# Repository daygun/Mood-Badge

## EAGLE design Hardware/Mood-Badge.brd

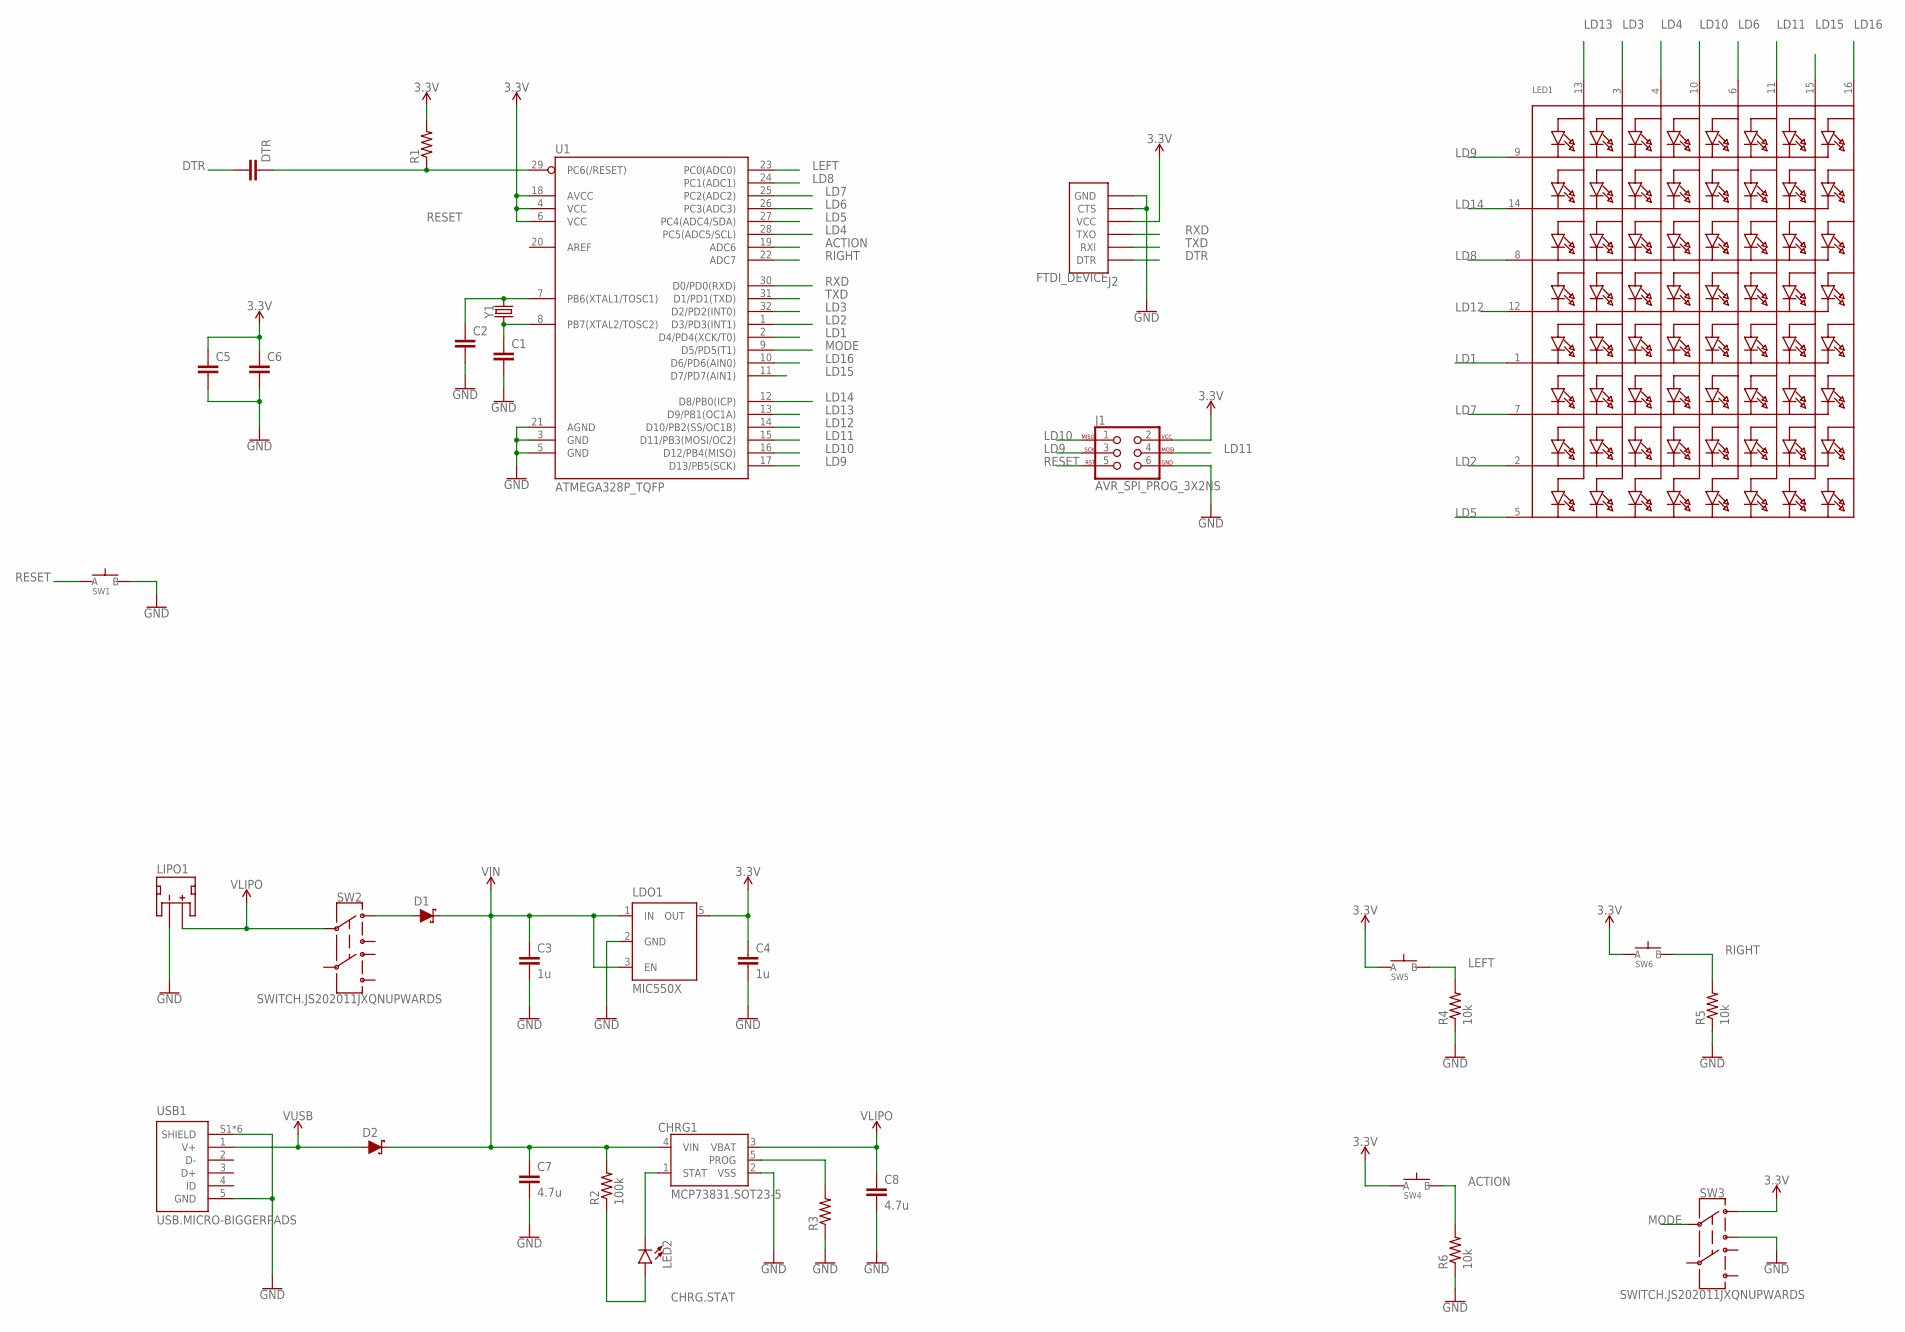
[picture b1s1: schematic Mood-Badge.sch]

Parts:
C1, C2, C5, C6: CAPACITOR0603; C0603
C3, C4: 1u; C0603
C7, C8: 4.7u; C0603
CHRG1: MCP73831.SOT23-5; SOT23-5
D1, D2: SCHOTTKY-USC; USC
DTR: CAPACITOR0603; C0603
J1: AVR_SPI_PROG_3X2NS; 2X3-NS
J2: FTDI_DEVICE
LDO1: MIC550X; SOT23-5
LED1: DOTMATRIX_8X8_ROWCATHODEM12A881UR; DOTMATRIX_BL-M12A881UR
LED2: LED0805; LED-0805
LIPO1: JST_2MM_MALE; JST-2-SMD
R1, R3: RESISTOR0603; R0603
R2: 100k; R0603
R4, R5, R6: 10k; R0603
SW1, SW4, SW5, SW6: SPST.KT11P4SM34LFS
SW2, SW3: SWITCH.JS202011JXQNUPWARDS; SWITCH.00
U1: ATMEGA328P_TQFP; TQFP32-08
USB1: USB.MICRO-BIGGERPADS; USB-MICRO-01.BIGGERPADS
Y1: CRYSTAL-CA-310; CA-301

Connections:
3.3V: C4.1, C5.1, C6.1, J1.2, J2.VCC, LDO1.5 (OUT), R1.2, SW3.1, SW4.1 (A), SW4.2 (A), SW5.1 (A), SW5.2 (A), SW6.1 (A), SW6.2 (A), U1.4 (VCC), U1.6 (VCC), U1.18 (AVCC)
ACTION: R6.2, SW4.3 (B), SW4.4 (B), U1.19 (ADC6)
CHRG.STAT: LED2.A, R2.1
DTR: DTR.1, J2.DTR
GND: C1.2, C2.2, C3.2, C4.2, C5.2, C6.2, C7.2, C8.2, CHRG1.2 (VSS), J1.6, J2.CTS, J2.GND, LDO1.2 (GND), LIPO1.1 (-), R3.1, R4.1, R5.1, R6.1, SW1.3 (B), SW1.4 (B), SW3.3, U1.3 (GND), U1.5 (GND), U1.21 (AGND), USB1.5 (GND), USB1.S1 (SHIELD), USB1.S2 (SHIELD), USB1.S3 (SHIELD), USB1.S4 (SHIELD), USB1.S5 (SHIELD), USB1.S6 (SHIELD)
LD1: LED1.1 (K5), U1.2 (D4/PD4(XCK/T0))
LD2: LED1.2 (K7), U1.1 (D3/PD3(INT1))
LD3: LED1.3 (A2), U1.32 (D2/PD2(INT0))
LD4: LED1.4 (A3), U1.28 (PC5(ADC5/SCL))
LD5: LED1.5 (K8), U1.27 (PC4(ADC4/SDA))
LD6: LED1.6 (A5), U1.26 (PC3(ADC3))
LD7: LED1.7 (K6), U1.25 (PC2(ADC2))
LD8: LED1.8 (K3), U1.24 (PC1(ADC1))
LD9: J1.3, LED1.9 (K1), U1.17 (D13/PB5(SCK))
LD10: J1.1, LED1.10 (A4), U1.16 (D12/PB4(MISO))
LD11: J1.4, LED1.11 (A6), U1.15 (D11/PB3(MOSI/OC2))
LD12: LED1.12 (K4), U1.14 (D10/PB2(SS/OC1B))
LD13: LED1.13 (A1), U1.13 (D9/PB1(OC1A))
LD14: LED1.14 (K2), U1.12 (D8/PB0(ICP))
LD15: LED1.15 (A7), U1.11 (D7/PD7(AIN1))
LD16: LED1.16 (A8), U1.10 (D6/PD6(AIN0))
LEFT: R4.2, SW5.3 (B), SW5.4 (B), U1.23 (PC0(ADC0))
MODE: SW3.2, U1.9 (D5/PD5(T1))
unnamed: C1.1, U1.8 (PB7(XTAL2/TOSC2)), Y1.1
unnamed: CHRG1.1 (STAT), LED2.C
unnamed: D1.+ (A), SW2.1
unnamed: C2.1, U1.7 (PB6(XTAL1/TOSC1)), Y1.2
unnamed: CHRG1.5 (PROG), R3.2
RESET: DTR.2, J1.5, R1.1, SW1.1 (A), SW1.2 (A), U1.29 (PC6(/RESET))
RIGHT: R5.2, SW6.3 (B), SW6.4 (B), U1.22 (ADC7)
RXD: J2.RXI (TXO), U1.30 (D0/PD0(RXD))
TXD: J2.TXO (RXI), U1.31 (D1/PD1(TXD))
VIN: C3.1, C7.1, CHRG1.4 (VIN), D1.- (C), D2.- (C), LDO1.1 (IN), LDO1.3 (EN), R2.2
VLIPO: C8.1, CHRG1.3 (VBAT), LIPO1.2 (+), SW2.2
V_USB: D2.+ (A), USB1.1 (V+)

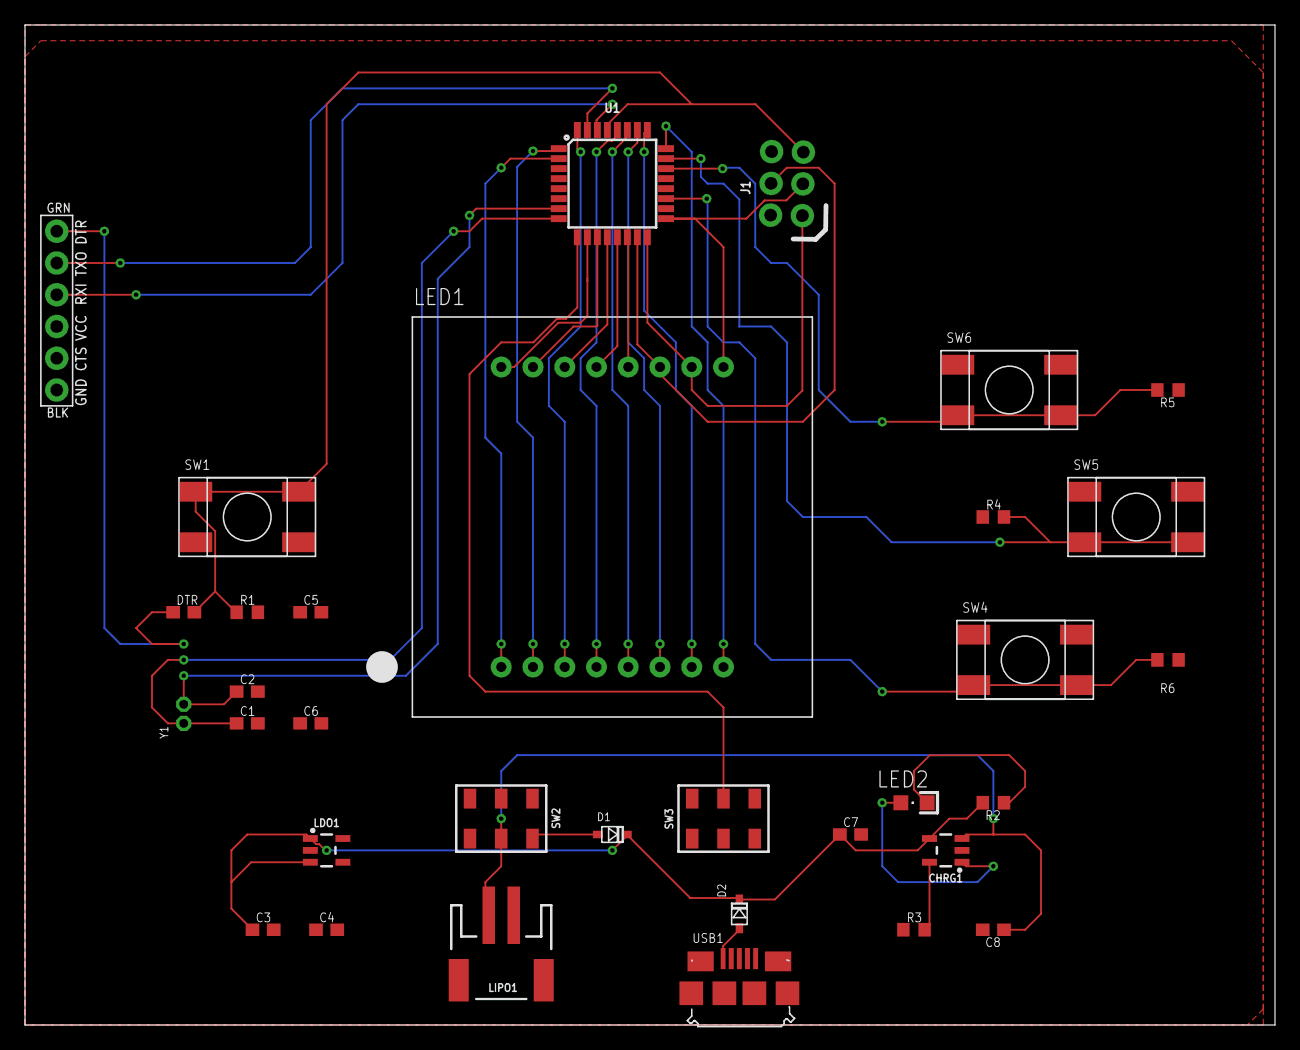
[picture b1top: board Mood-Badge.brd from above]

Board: 2 copper layers, 100.0 x 80.0 mm, 33 parts (0 on the bottom side), 35 nets.

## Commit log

2022-09-07 features list
2022-09-14 dding the BOM file
2022-09-14 day 2
2022-09-15 atmega schematics is now establish/included.
2022-09-21 Power management circuit still in progress, bootload, ftdi, and LED matrix is done.
2022-09-22 day 3 changs
2022-09-28 the schematic is ready, the LED for the power managemnet circuit should still be added.
2022-09-28 added LED
2022-09-29 board layout done, wiring is in progress
2022-09-29 wiring is done
2022-10-05 polygone is done
2022-10-06 drc errors fixed
